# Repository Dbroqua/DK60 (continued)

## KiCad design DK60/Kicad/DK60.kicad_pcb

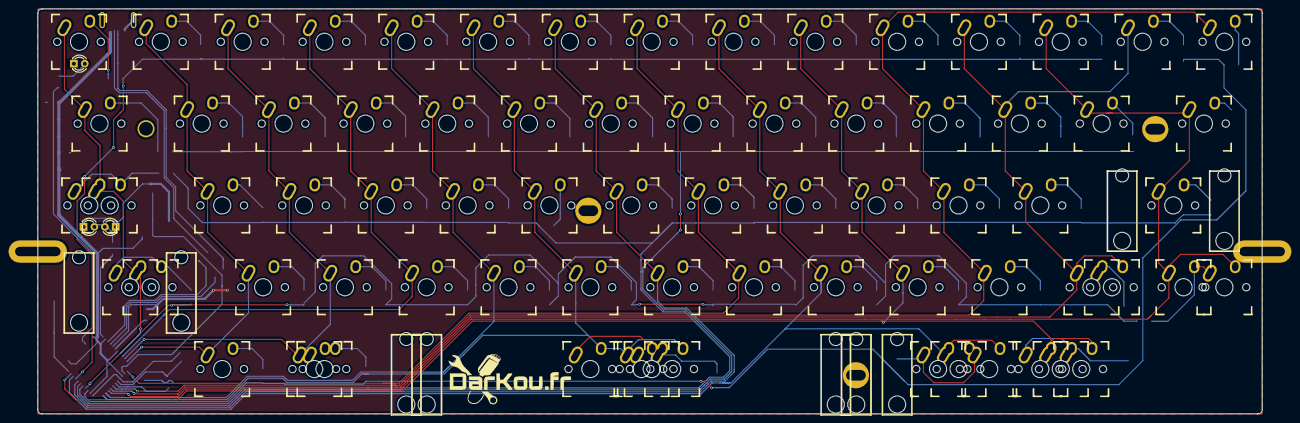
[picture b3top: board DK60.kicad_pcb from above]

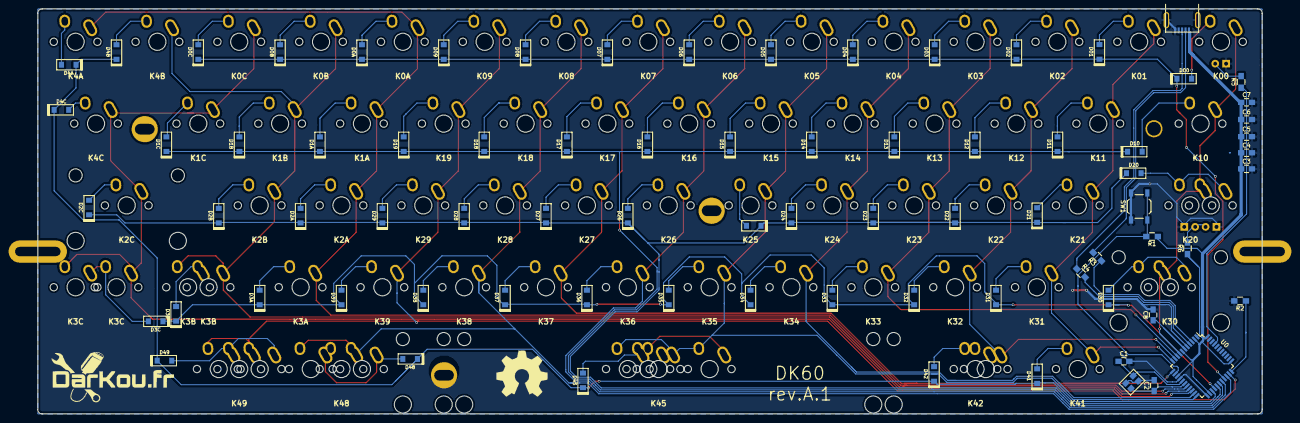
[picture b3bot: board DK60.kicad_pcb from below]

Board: 2 copper layers, 285.1 x 94.3 mm, 168 parts (78 on the bottom side), 93 nets.

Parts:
C1, C2: 22p; C_0805_HandSoldering
C3, C4, C5, C6: 0.1u; C_0805_HandSoldering
C7: 4.7u; C_0805_HandSoldering
C8: 1u; C_0805_HandSoldering
D1: D00; D_SOD123
D2: D01; D_SOD123
D3: D02; D_SOD123
D4: D03; D_SOD123
D5: D04; D_SOD123
D6: D05; D_SOD123
D7: D06; D_SOD123
D8: D07; D_SOD123
D9: D08; D_SOD123
D10: D09; D_SOD123
D11: D0A; D_SOD123
D12: D0B; D_SOD123
D13: D0C; D_SOD123
D14: D10; D_SOD123
D15: D11; D_SOD123
D16: D12; D_SOD123
D17: D13; D_SOD123
D18: D14; D_SOD123
D19: D15; D_SOD123
D20: D16; D_SOD123
D21: D17; D_SOD123
D22: D18; D_SOD123
D23: D19; D_SOD123
D24: D1A; D_SOD123
D25: D1B; D_SOD123
D26: D1C; D_SOD123
D27: D20; D_SOD123
D28: D21; D_SOD123
D29: D22; D_SOD123
D30: D23; D_SOD123
D31: D24; D_SOD123
D32: D25; D_SOD123
D33: D26; D_SOD123
D34: D27; D_SOD123
D35: D28; D_SOD123
D36: D29; D_SOD123
D37: D2A; D_SOD123
D38: D2B; D_SOD123
D39: D2C; D_SOD123
D40: D30; D_SOD123
D41: D31; D_SOD123
D42: D32; D_SOD123
D43: D33; D_SOD123
D44: D34; D_SOD123
D45: D35; D_SOD123
D46: D36; D_SOD123
D47: D37; D_SOD123
D48: D38; D_SOD123
D49: D39; D_SOD123
D50: D3A; D_SOD123
D51: D3B; D_SOD123
D52: D3C; D_SOD123
D53: D41; D_SOD123
D54: D42; D_SOD123
D55: D45; D_SOD123
D56: D48; D_SOD123
D57: D49; D_SOD123
D58: D4A; D_SOD123
D59: D4B; D_SOD123
D60: D4C; D_SOD123
HOLE_M3: VAL**; HOLE_M3
J1: USB_mini_micro_B; USB_miniB_hirose_5S8
K1: K00; Mx_Alps_100
K2: K01; Mx_Alps_100
K3: K02; Mx_Alps_100
K4: K03; Mx_Alps_100
K5: K04; Mx_Alps_100
K6: K05; Mx_Alps_100
K7: K06; Mx_Alps_100
K8: K07; Mx_Alps_100
K9: K08; Mx_Alps_100
K10: K09; Mx_Alps_100
K11: K0A; Mx_Alps_100
K12: K0B; Mx_Alps_100
K13: K0C; Mx_Alps_100
K14: K10; Mx_Alps_150
K15: K11; Mx_Alps_100
K16: K12; Mx_Alps_100
K17: K13; Mx_Alps_100
K18: K14; Mx_Alps_100
K19: K15; Mx_Alps_100
K20: K16; Mx_Alps_100
K21: K17; Mx_Alps_100
K22: K18; Mx_Alps_100
K23: K19; Mx_Alps_100
K24: K1A; Mx_Alps_100
K25: K1B; Mx_Alps_100
K26: K1C; Mx_Alps_100
K27: K20; Mx_Alps_175
K28: K21; Mx_Alps_100
K29: K22; Mx_Alps_100
K30: K23; Mx_Alps_100
K31: K24; Mx_Alps_100
K32: K25; Mx_Alps_100
K33: K26; Mx_Alps_100
K34: K27; Mx_Alps_100
K35: K28; Mx_Alps_100
K36: K29; Mx_Alps_100
K37: K2A; Mx_Alps_100
K38: K2B; Mx_Alps_100
K39: K2C; Mx_Alps_225
K40: K30; Mx_Alps_175
K41: K31; Mx_Alps_100
K42: K32; Mx_Alps_100
K43: K33; Mx_Alps_100
K44: K34; Mx_Alps_100
K45: K35; Mx_Alps_100
K46: K36; Mx_Alps_100
K47: K37; Mx_Alps_100
K48: K38; Mx_Alps_100
K49: K39; Mx_Alps_100
K50: K3A; Mx_Alps_100
K51: K3B; Mx_Alps_125
K52, K70: K3C; Mx_Alps_100
K53: K41; Mx_Alps_100
K54: K42; Mx_Alps_150
K55: K45; Mx_Alps_625
K56: K48; Mx_Alps_150
K57: K49; Mx_Alps_100
K58: K4A; Mx_Alps_100
K59: K4B; Mx_Alps_100
K60: K4C; Mx_Alps_150
K61: Ctrl; Mx_Alps_175_STEPPED
K62: L_ALT; Mx_Alps_125
K63: SPACE; Mx_Alps_700
K64: SPACE; Mx_Alps_600
K65: R_ALT; Mx_Alps_125
K66: R_ALT; Mx_Alps_150
K67, K68: R_GUI; Mx_Alps_100
K69: K30; Mx_Alps_225
K71: K3B; Mx_Alps_175
K72: SPACE; Mx_Alps_100
LD0: ESC_LED; LED_D3.0mm
LD1, LD2: CAPS_LED; LED_D3.0mm
MXST: VAL**; MXST
MXST#2, MXST#3, MXST#4, MXST#5, MXST#6, MXST#7, MXST#8, MXST#9: VAL**; MXST
Poker_oval_hole: VAL**; Poker_oval_hole
Poker_oval_hole#2, Poker_oval_hole#3: VAL**; Poker_oval_hole
Poker_side_edge_long: VAL**; Poker_side_edge_long
Poker_side_edge_long#2: VAL**; Poker_side_edge_long
R1, R2: 10K; R_0805_HandSoldering
R3, R4: 22; R_0805_HandSoldering
R5, R6: R; R_0805_HandSoldering
SW1: SW_PUSH; SW_SPST_TL3342
U0: ATMEGA32U4; TQFP-44_10x10mm_Pitch0.8mm
X1: XTAL_GND; FA-238

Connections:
/CAPS_LED: R6.1, U0.1
/Col0: K1.1, K14.1, K27.1, K40.1, K61.2, K69.2, U0.8
/Col1: K2.1, K15.1, K28.1, K41.1, K53.1, U0.11
/Col2: K3.1, K16.1, K29.1, K42.1, K54.1, K62.1, U0.10
/Col3: K4.1, K17.1, K30.1, K43.1, U0.9
/Col4: K5.1, K18.1, K31.1, K44.1, U0.21
/Col5: K6.1, K19.1, K32.1, K45.1, K55.1, K63.1, K64.2, K72.2, U0.22
/Col6: K7.1, K20.1, K33.1, K46.1, U0.29
/Col7: K8.1, K21.1, K34.1, K47.1, U0.12
/Col8: K9.1, K22.1, K35.1, K48.1, K56.1, K65.2, K66.2, U0.31
/Col9: K10.1, K23.1, K36.1, K49.1, K57.1, K67.2, K68.2, U0.32
/Col10: K11.1, K24.1, K37.1, K50.1, K58.1, U0.18
/Col11: K12.1, K25.1, K38.1, K51.1, K59.1, K71.2, U0.19
/Col12: K13.1, K26.1, K39.1, K52.1, K60.1, K70.2, U0.20
/ESC_LED: R5.1, U0.41
/Row0: D1.1, D2.1, D3.1, D4.1, D5.1, D6.1, D7.1, D8.1, D9.1, D10.1, D11.1, D12.1, D13.1, U0.30
/Row1: D14.1, D15.1, D16.1, D17.1, D18.1, D19.1, D20.1, D21.1, D22.1, D23.1, D24.1, D25.1, D26.1, U0.28
/Row2: D27.1, D28.1, D29.1, D30.1, D31.1, D32.1, D33.1, D34.1, D35.1, D36.1, D37.1, D38.1, D39.1, U0.27
/Row3: D40.1, D41.1, D42.1, D43.1, D44.1, D45.1, D46.1, D47.1, D48.1, D49.1, D50.1, D51.1, D52.1, U0.26
/Row4: D53.1, D54.1, D55.1, D56.1, D57.1, D58.1, D59.1, D60.1, U0.25
GND: C1.2, C2.2, C3.2, C4.2, C5.2, C6.2, C7.2, C8.2, J1.5, J1.6, LD0.1, LD1.1, LD2.1, R2.2, SW1.1, U0.5, U0.15, U0.23, X1.3
unnamed: C1.1, U0.16, X1.1
unnamed: C2.1, U0.17, X1.2
unnamed: C8.1, U0.6
unnamed: D1.2, K1.2
unnamed: D2.2, K2.2
unnamed: D3.2, K3.2
unnamed: D4.2, K4.2
unnamed: D5.2, K5.2
unnamed: D6.2, K6.2
unnamed: D7.2, K7.2
unnamed: D8.2, K8.2
unnamed: D9.2, K9.2
unnamed: D10.2, K10.2
unnamed: D11.2, K11.2
unnamed: D12.2, K12.2
unnamed: D13.2, K13.2
unnamed: D14.2, K14.2
unnamed: D15.2, K15.2
unnamed: D16.2, K16.2
unnamed: D17.2, K17.2
unnamed: D18.2, K18.2
unnamed: D19.2, K19.2
unnamed: D20.2, K20.2
unnamed: D21.2, K21.2
unnamed: D22.2, K22.2
unnamed: D23.2, K23.2
unnamed: D24.2, K24.2
unnamed: D25.2, K25.2
unnamed: D26.2, K26.2
unnamed: D27.2, K27.2, K61.1
unnamed: D28.2, K28.2
unnamed: D29.2, K29.2
unnamed: D30.2, K30.2
unnamed: D31.2, K31.2
unnamed: D32.2, K32.2
unnamed: D33.2, K33.2
unnamed: D34.2, K34.2
unnamed: D35.2, K35.2
unnamed: D36.2, K36.2
unnamed: D37.2, K37.2
unnamed: D38.2, K38.2
unnamed: D39.2, K39.2
unnamed: D40.2, K40.2, K69.1
unnamed: D41.2, K41.2
unnamed: D42.2, K42.2
unnamed: D43.2, K43.2
unnamed: D44.2, K44.2
unnamed: D45.2, K45.2
unnamed: D46.2, K46.2
unnamed: D47.2, K47.2
unnamed: D48.2, K48.2
unnamed: D49.2, K49.2
unnamed: D50.2, K50.2
unnamed: D51.2, K51.2, K71.1
unnamed: D52.2, K52.2, K70.1
unnamed: D53.2, K53.2
unnamed: D54.2, K54.2, K62.2
unnamed: D55.2, K55.2, K63.2, K64.1, K72.1
unnamed: D56.2, K56.2, K65.1, K66.1
unnamed: D57.2, K57.2, K67.1, K68.1
unnamed: D58.2, K58.2
unnamed: D59.2, K59.2
unnamed: D60.2, K60.2
unnamed: J1.2, R3.2
unnamed: J1.3, R4.1
unnamed: LD0.2, R5.2
unnamed: LD1.2, LD2.2, R6.2
unnamed: R1.2, SW1.2, U0.13
unnamed: R2.1, U0.33
unnamed: R3.1, U0.3
unnamed: R4.2, U0.4
VCC: C3.1, C4.1, C5.1, C6.1, C7.1, J1.1, R1.1, U0.2, U0.7, U0.14, U0.24, U0.34, U0.44

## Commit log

2017-04-30 - Added Kicad source files
2017-04-30 - Updated position of Atmega and Crystal - Added render view
2017-04-30 - Updated readme with some previews
2017-04-30 Update README.md
    Fixed bug in README.md
2017-04-30 - Updated gitignore file
2017-04-30 - Added 175 stepped Ctrontrol key
2017-04-30 - Added footprint for 6U and 7U spacebar
2017-04-30 - Added Poker Hole - Added Poker plate (dxf and svg) - Updated render and layout preview
2017-04-30 - Updated poker plate: added stepped control key and redraw holes and borders
2017-05-01 - Added darkou and open hardware logo - Updated col/row assignation (simplifying rooting)
2017-05-01 - Updated README file
2017-05-01 - Rerouting some wires - Added led on Esc and Caps locks switches
2017-05-02 - Some routing updates
2017-05-02 - Cleaning routing, again and again
2017-05-04 - Updated layout to allow choice in 3 combinations for bottom row
2017-05-05 - Updated bottom row
2017-05-05 - Added gerber files
2017-05-05 - Removed switch.svf - Updated poker plate (added 4 plates in one file, all possible bottom row)
2017-05-07 - Updated switches label (K00 to K4C) - Fixed footprint - Updated gerber files
2017-05-08 - Replaced all Diodes with SMD
2017-05-13 - Updated footprints - Fixed some bugs (position of holes)
2017-05-13 - Some updates in routing
2017-05-14 - Routing, again and again - Naming all Diodes - Fixed some bugs for holes - Added holes for PCB stabilizers
2017-05-15 - Updated with of tracks for Vcc/Gnd
2017-05-23 - Updated plate.dxf (now use layers to simulate all available layouts\n- Added revert 6u spacebar
2017-05-23 - Updated plate.dxf (now use layers to simulate all available layouts) - Added revert 6u spacebar
2017-05-24 - Removed useless layer for plate - Fixed bug in plate.dxf
2017-05-24 - Fixed bug for bottom hole in PCB - Generated Gerber files
2017-05-24 - Moved d25
2017-05-24 - Removed comment lines
2017-05-27 - Reorganize repo to split DK60 and DK60TP
2017-05-27 - Added Trackpoint files (for 3d printing)
2017-05-27 - Added PCB for DK60TP
2017-05-28 - Replaced caps lock led with SMD (DK60TP)
2017-05-28 - Added 3D models for Cherry switches
2017-05-28 - DK60TP: Changed rows/cols assignation to simplify routing
2017-05-28 - Added documentation for TPM754
2017-05-29 Added picture of DK60 PCB
2017-05-29 - Fixed bug in DK60 (row2/GND) - Added Gerber files for DK60
2017-05-30 - Updated Led position - Fixed bug for bottom hole - Updated gerber files
2017-05-31 - Updated 3D parts for trackpoint
2017-05-31 - Added missing file for previous update...
2017-06-01 - Rewrote all for DK60TP
2017-06-02 - Added MouseButtons project - Updated DK60TP - Updated readme
2017-06-02 - DK60TP: reducing quantity of VIAs
2017-06-03 - DK60TP: updated routing and reducing quantity of vias (again)
2017-06-03 - Moved back logo
2017-06-03 - Added libraries/footprint from mohitg11 (TS65) - Added Backlit for DK60TP (need to fix bug for bottom row)
2017-06-04 - Updated README - Added Cherry's footprints - Removed ALPS compatibity for DK60TP
2017-06-04 - Updated routing - Updated LED_TH_BIVAR
2017-06-04 - Added some documentation (Teensy pineout, PAM2804, WS2812B, MX mounting holes...)
2017-06-04 - Added documentation for ATmega and DMC3021LSD
2017-06-04 - DK60TP: Updated ods file for assignation keycode/placement
2017-06-04 - DK60TP: Updated layout possibility - DK60TP: Split schematic in some files
2017-06-05 - DK60TP: Moved Matrix in separate schematic file - DK60TP: Added holes in schematic file
2017-06-05 - DK60TP: added missing schematic files
2017-06-05 - DK60TP: Added RGB underglow
2017-06-05 - Added documentation for Power inductor
2017-06-05 - DK60TP: Added readme with parts (RFC)
2017-06-06 - DK60TP: Some changes on PCB (routing)
2017-06-06 - DK60TP: Added tmp files for sandwich case
2017-06-06 - Dk60TP: Added all in one case file
2017-06-07 - DK60TP: All top plates designed
2017-06-07 - DK60TP: First revision for All in one cases (need verifications of dimensions)
2017-06-07 - DK60TP: Updated sandwich case
2017-06-07 - DK60TP: renamed sandwich case file name
2017-06-07 - DK60TP: Deleted tmp file for case
2017-06-08 - DK60TP: added holes for feet in sandwich case
2017-06-08 - DK60TP: Removed bug in sandwich case
2017-06-10 - DK60TP: Added ods file for sandwich case - DK60TP: Updated dxf file
2017-06-10 - DK60TP: All in one PCB
2017-06-10 - Updated README
2017-06-10 - DK60TP: Added holes for Mouse button's PCB
2017-06-11 - DK60TP: Added RGB underglow on Mouse PCB
2017-06-11 - DK60TP: Replaced connector for trackpoint (Molex PicoBlade)
2017-06-11 - DK60TP: Fixed bug for previews
2017-06-12 - DK60TP: Updated routing
2017-06-12 -DK60TP: Fixed name for RMB switch
2017-06-12 - DK60TP: Replaced correctly RGB leds in mouse buttons PCB
2017-06-13 - DK60TP: Updated Crystal position - DK60TP: Fixed labels for connectors - DK60TP: Updated routing
2017-06-14 - Moved DK60YP to is dedicaded project
